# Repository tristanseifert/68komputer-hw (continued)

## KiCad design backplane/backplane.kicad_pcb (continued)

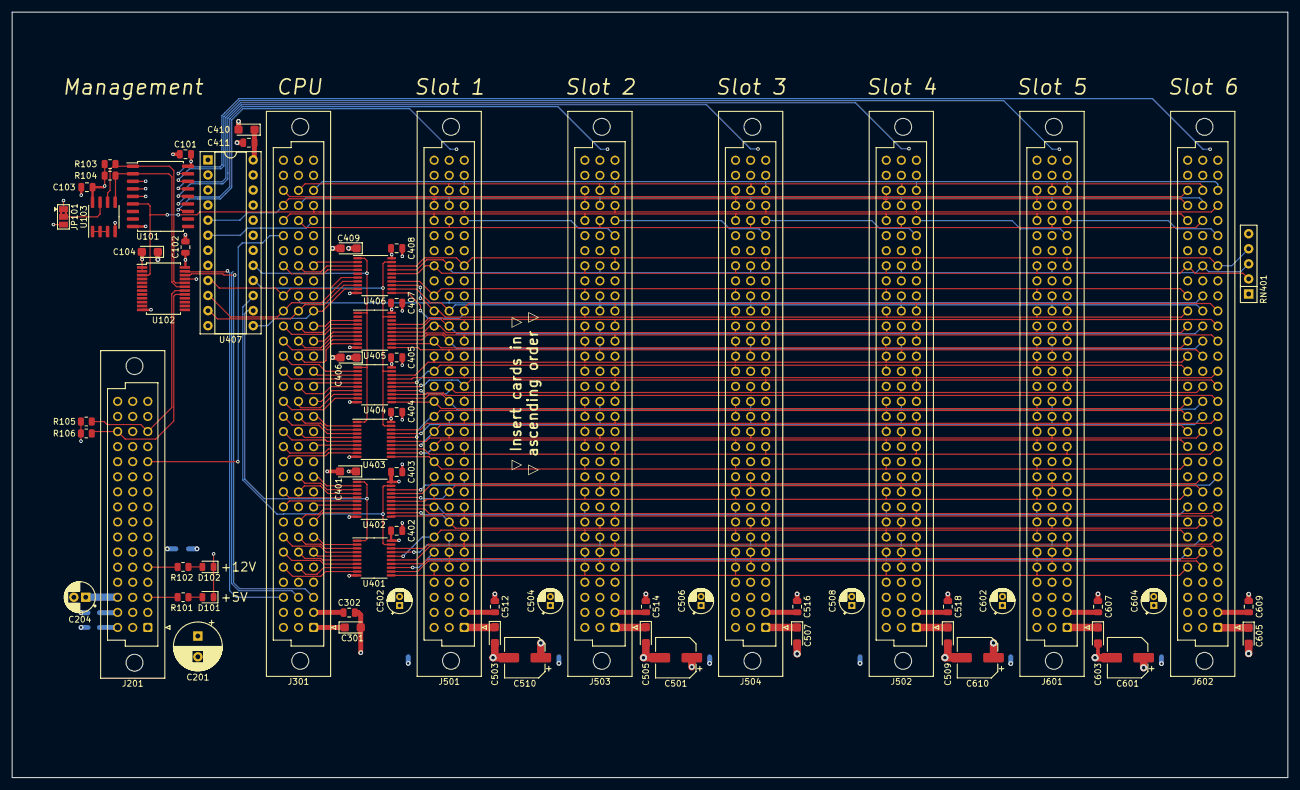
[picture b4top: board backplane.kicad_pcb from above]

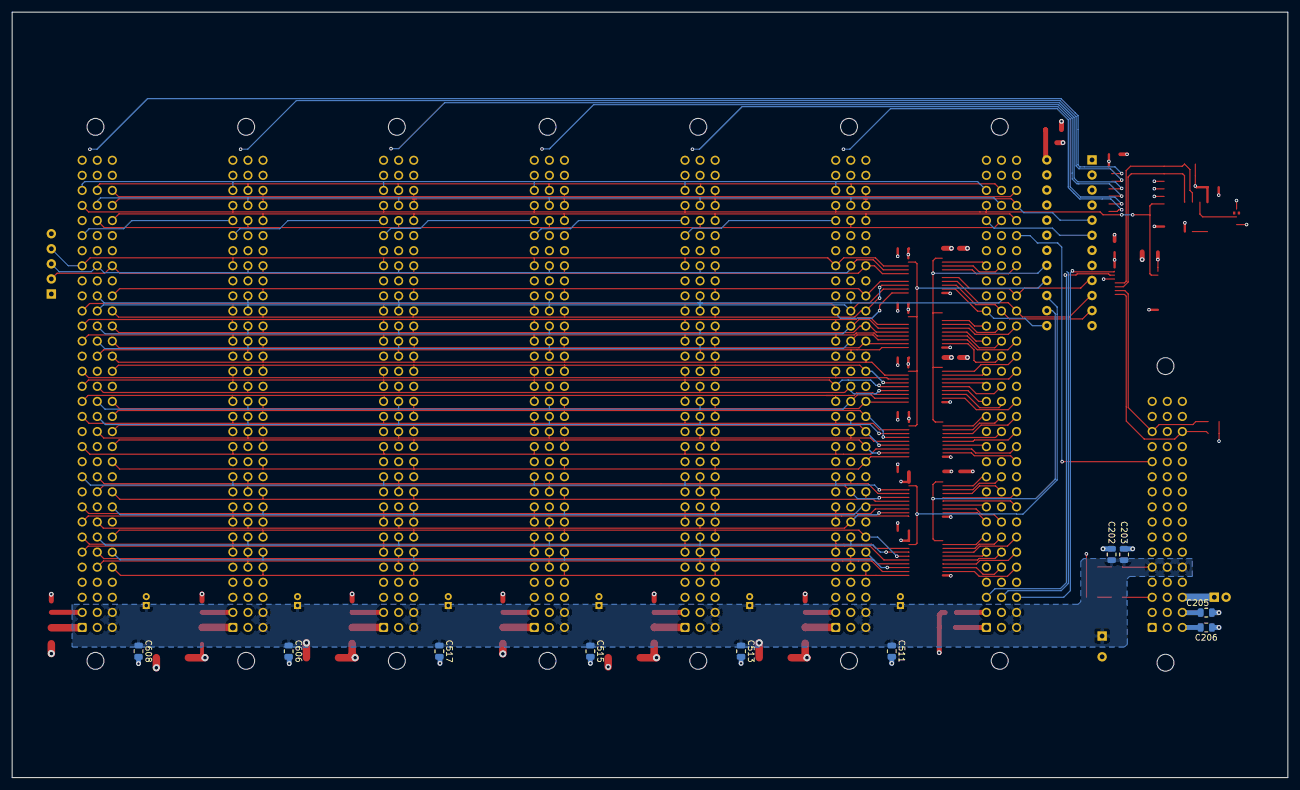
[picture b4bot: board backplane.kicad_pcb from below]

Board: 4 copper layers, 215.0 x 129.0 mm, 79 parts (10 on the bottom side), 132 nets.

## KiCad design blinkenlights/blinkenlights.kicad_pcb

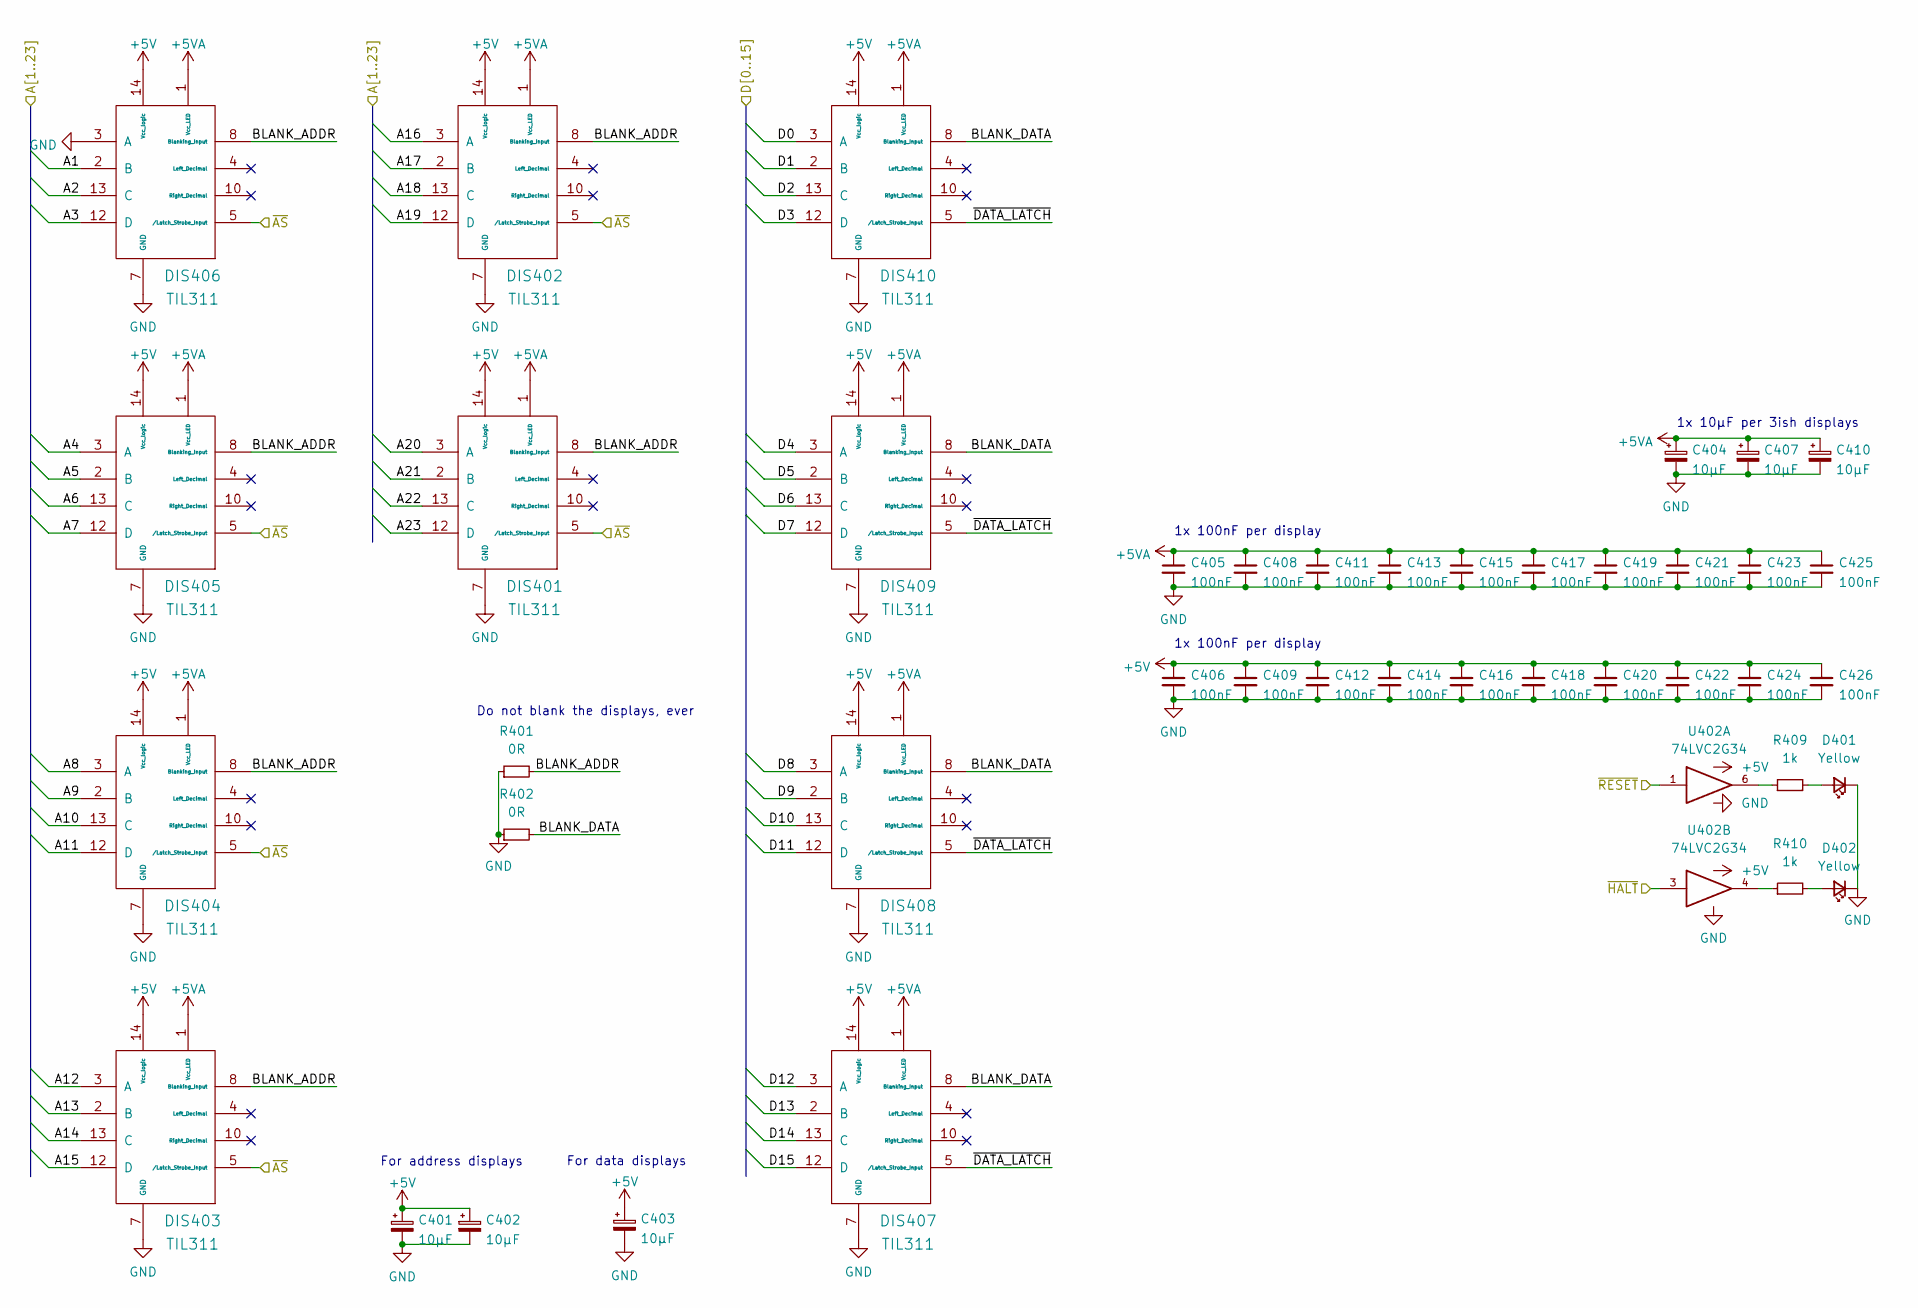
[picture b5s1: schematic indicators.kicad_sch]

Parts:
C401, C402, C403, C404, C407, C410: 10µF; CP_EIA-3216-18_Kemet-A; MPN TAJB106K025SNJ
C405, C406, C408, C409, C411, C412, C413, C414, C415, C416, C417, C418, C419, C420, C421, C422, C423, C424, C425, C426: 100nF; C_0805_2012Metric
D401, D402: Yellow; LED_0805_2012Metric; MPN AP2012YD
DIS401, DIS402, DIS403, DIS404, DIS405, DIS406, DIS407, DIS408, DIS409, DIS410: TIL311
R401, R402: 0R; R_0805_2012Metric; MPN RC0805JR-100RL
R409, R410: 1k; R_0805_2012Metric
U402: 74LVC2G34; SOT-363_SC-70-6_Handsoldering; MPN 74LVC2G34DW-7

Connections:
+5V: C401.1, C402.1, C403.1, C406.1, C409.1, C412.1, C414.1, C416.1, C418.1, C420.1, C422.1, C424.1, C426.1, DIS401.14 (Vcc_logic), DIS402.14 (Vcc_logic), DIS403.14 (Vcc_logic), DIS404.14 (Vcc_logic), DIS405.14 (Vcc_logic), DIS406.14 (Vcc_logic), DIS407.14 (Vcc_logic), DIS408.14 (Vcc_logic), DIS409.14 (Vcc_logic), DIS410.14 (Vcc_logic), U402.5 (VCC); also elsewhere on the board
+5VA: C404.1, C405.1, C407.1, C408.1, C410.1, C411.1, C413.1, C415.1, C417.1, C419.1, C421.1, C423.1, C425.1, DIS401.1 (Vcc_LED), DIS402.1 (Vcc_LED), DIS403.1 (Vcc_LED), DIS404.1 (Vcc_LED), DIS405.1 (Vcc_LED), DIS406.1 (Vcc_LED), DIS407.1 (Vcc_LED), DIS408.1 (Vcc_LED), DIS409.1 (Vcc_LED), DIS410.1 (Vcc_LED); also elsewhere on the board
/A1: DIS406.2 (B); also elsewhere on the board
/A2: DIS406.13 (C); also elsewhere on the board
/A3: DIS406.12 (D); also elsewhere on the board
/A4: DIS405.3 (A); also elsewhere on the board
/A5: DIS405.2 (B); also elsewhere on the board
/A6: DIS405.13 (C); also elsewhere on the board
/A7: DIS405.12 (D); also elsewhere on the board
/A8: DIS404.3 (A); also elsewhere on the board
/A9: DIS404.2 (B); also elsewhere on the board
/A10: DIS404.13 (C); also elsewhere on the board
/A11: DIS404.12 (D); also elsewhere on the board
/A12: DIS403.3 (A); also elsewhere on the board
/A13: DIS403.2 (B); also elsewhere on the board
/A14: DIS403.13 (C); also elsewhere on the board
/A15: DIS403.12 (D); also elsewhere on the board
/A16: DIS402.3 (A); also elsewhere on the board
/A17: DIS402.2 (B); also elsewhere on the board
/A18: DIS402.13 (C); also elsewhere on the board
/A19: DIS402.12 (D); also elsewhere on the board
/A20: DIS401.3 (A); also elsewhere on the board
/A21: DIS401.2 (B); also elsewhere on the board
/A22: DIS401.13 (C); also elsewhere on the board
/A23: DIS401.12 (D); also elsewhere on the board
/D0: DIS410.3 (A); also elsewhere on the board
/D1: DIS410.2 (B); also elsewhere on the board
/D2: DIS410.13 (C); also elsewhere on the board
/D3: DIS410.12 (D); also elsewhere on the board
/D4: DIS409.3 (A); also elsewhere on the board
/D5: DIS409.2 (B); also elsewhere on the board
/D6: DIS409.13 (C); also elsewhere on the board
/D7: DIS409.12 (D); also elsewhere on the board
/D8: DIS408.3 (A); also elsewhere on the board
/D9: DIS408.2 (B); also elsewhere on the board
/D10: DIS408.13 (C); also elsewhere on the board
/D11: DIS408.12 (D); also elsewhere on the board
/D12: DIS407.3 (A); also elsewhere on the board
/D13: DIS407.2 (B); also elsewhere on the board
/D14: DIS407.13 (C); also elsewhere on the board
/D15: DIS407.12 (D); also elsewhere on the board
/Displays and Indicators/BLANK_ADDR: DIS401.8 (Blanking_Input), DIS402.8 (Blanking_Input), DIS403.8 (Blanking_Input), DIS404.8 (Blanking_Input), DIS405.8 (Blanking_Input), DIS406.8 (Blanking_Input), R401.2
/Displays and Indicators/BLANK_DATA: DIS407.8 (Blanking_Input), DIS408.8 (Blanking_Input), DIS409.8 (Blanking_Input), DIS410.8 (Blanking_Input), R402.2
/Displays and Indicators/~DATA_LATCH: DIS407.5 (/Latch_Strobe_Input), DIS408.5 (/Latch_Strobe_Input), DIS409.5 (/Latch_Strobe_Input), DIS410.5 (/Latch_Strobe_Input)
/~AS: DIS401.5 (/Latch_Strobe_Input), DIS402.5 (/Latch_Strobe_Input), DIS403.5 (/Latch_Strobe_Input), DIS404.5 (/Latch_Strobe_Input), DIS405.5 (/Latch_Strobe_Input), DIS406.5 (/Latch_Strobe_Input); also elsewhere on the board
/~HALT: U402.3; also elsewhere on the board
/~RESET: U402.1; also elsewhere on the board
GND: C401.2, C402.2, C403.2, C404.2, C405.2, C406.2, C407.2, C408.2, C409.2, C410.2, C411.2, C412.2, C413.2, C414.2, C415.2, C416.2, C417.2, C418.2, C419.2, C420.2, C421.2, C422.2, C423.2, C424.2, C425.2, C426.2, D401.1 (K), D402.1 (K), DIS401.7 (GND), DIS402.7 (GND), DIS403.7 (GND), DIS404.7 (GND), DIS405.7 (GND), DIS406.3 (A), DIS406.7 (GND), DIS407.7 (GND), DIS408.7 (GND), DIS409.7 (GND), DIS410.7 (GND), R401.1, R402.1, U402.2 (GND); also elsewhere on the board
unnamed: D401.2 (A), R409.2
unnamed: D402.2 (A), R410.2
unnamed: R409.1, U402.6
unnamed: R410.1, U402.4

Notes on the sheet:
1x 10µF per 3ish displays
1x 100nF per display
For address displays
For data displays
Do not blank the displays, ever

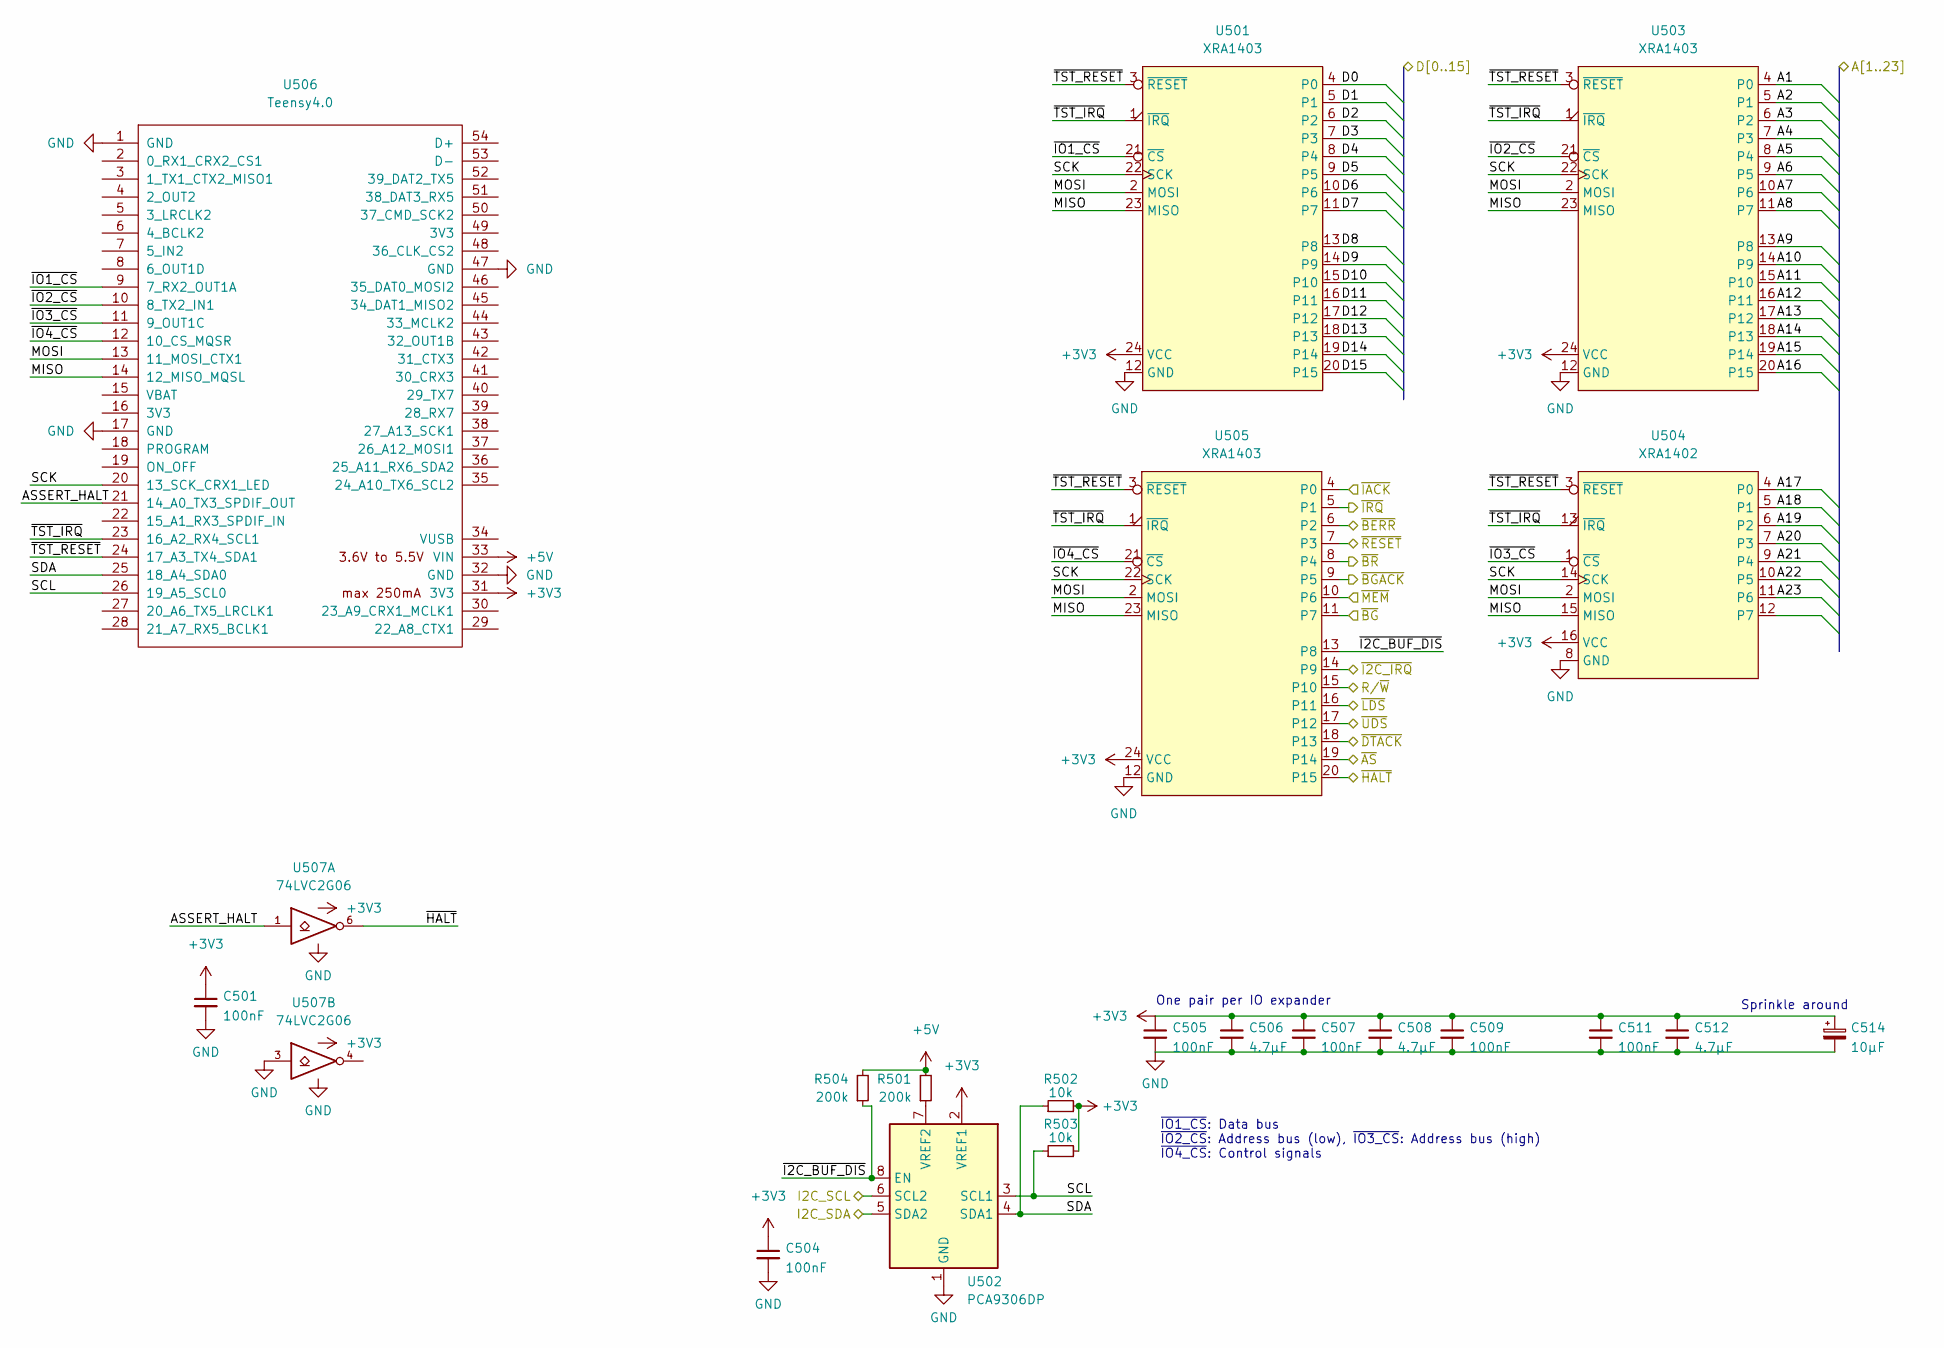
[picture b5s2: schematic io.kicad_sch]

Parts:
C501, C504, C505, C507, C509, C511: 100nF; C_0805_2012Metric
C506, C508, C512: 4.7µF; C_0805_2012Metric
C514: 10µF; CP_EIA-3216-18_Kemet-A; MPN TAJB106K025SNJ
R501, R504: 200k; R_0805_2012Metric
R502, R503: 10k; R_0805_2012Metric
U501, U503, U505: XRA1403; TSSOP-24_4.4x7.8mm_P0.65mm
U502: PCA9306DP; SO-8_3.9x4.9mm_P1.27mm
U504: XRA1402; TSSOP-16_4.4x5mm_P0.65mm
U506: Teensy4.0; Teensy40-NoBonus
U507: 74LVC2G06; SOT-23-6_Handsoldering

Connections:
+3V3: C501.1, C504.1, C505.1, C506.1, C507.1, C508.1, C509.1, C511.1, C512.1, C514.1, R502.2, R503.2, U501.24 (VCC), U502.2 (VREF1), U503.24 (VCC), U504.16 (VCC), U505.24 (VCC), U506.31 (3V3), U507.5 (VCC); also elsewhere on the board
+5V: R501.2, R504.2, U506.33 (VIN); also elsewhere on the board
/A1: U503.4 (P0); also elsewhere on the board
/A2: U503.5 (P1); also elsewhere on the board
/A3: U503.6 (P2); also elsewhere on the board
/A4: U503.7 (P3); also elsewhere on the board
/A5: U503.8 (P4); also elsewhere on the board
/A6: U503.9 (P5); also elsewhere on the board
/A7: U503.10 (P6); also elsewhere on the board
/A8: U503.11 (P7); also elsewhere on the board
/A9: U503.13 (P8); also elsewhere on the board
/A10: U503.14 (P9); also elsewhere on the board
/A11: U503.15 (P10); also elsewhere on the board
/A12: U503.16 (P11); also elsewhere on the board
/A13: U503.17 (P12); also elsewhere on the board
/A14: U503.18 (P13); also elsewhere on the board
/A15: U503.19 (P14); also elsewhere on the board
/A16: U503.20 (P15); also elsewhere on the board
/A17: U504.4 (P0); also elsewhere on the board
/A18: U504.5 (P1); also elsewhere on the board
/A19: U504.6 (P2); also elsewhere on the board
/A20: U504.7 (P3); also elsewhere on the board
/A21: U504.9 (P4); also elsewhere on the board
/A22: U504.10 (P5); also elsewhere on the board
/A23: U504.11 (P6); also elsewhere on the board
/D0: U501.4 (P0); also elsewhere on the board
/D1: U501.5 (P1); also elsewhere on the board
/D2: U501.6 (P2); also elsewhere on the board
/D3: U501.7 (P3); also elsewhere on the board
/D4: U501.8 (P4); also elsewhere on the board
/D5: U501.9 (P5); also elsewhere on the board
/D6: U501.10 (P6); also elsewhere on the board
/D7: U501.11 (P7); also elsewhere on the board
/D8: U501.13 (P8); also elsewhere on the board
/D9: U501.14 (P9); also elsewhere on the board
/D10: U501.15 (P10); also elsewhere on the board
/D11: U501.16 (P11); also elsewhere on the board
/D12: U501.17 (P12); also elsewhere on the board
/D13: U501.18 (P13); also elsewhere on the board
/D14: U501.19 (P14); also elsewhere on the board
/D15: U501.20 (P15); also elsewhere on the board
/I2C_SCL: U502.6 (SCL2); also elsewhere on the board
/I2C_SDA: U502.5 (SDA2); also elsewhere on the board
/IO Drivers/ASSERT_HALT: U506.21 (14_A0_TX3_SPDIF_OUT), U507.1
/IO Drivers/CTRL_DIR: U506.29 (22_A8_CTX1); also elsewhere on the board
/IO Drivers/MISO: U501.23 (MISO), U503.23 (MISO), U504.15 (MISO), U505.23 (MISO), U506.14 (12_MISO_MQSL)
/IO Drivers/MOSI: U501.2 (MOSI), U503.2 (MOSI), U504.2 (MOSI), U505.2 (MOSI), U506.13 (11_MOSI_CTX1)
/IO Drivers/R/~W_3V3: U506.27 (20_A6_TX5_LRCLK1); also elsewhere on the board
/IO Drivers/SCK: U501.22 (SCK), U503.22 (SCK), U504.14 (SCK), U505.22 (SCK), U506.20 (13_SCK_CRX1_LED)
/IO Drivers/SCL: R503.1, U502.3 (SCL1), U506.26 (19_A5_SCL0)
/IO Drivers/SDA: R502.1, U502.4 (SDA1), U506.25 (18_A4_SDA0)
/IO Drivers/~AS_3V3: U506.28 (21_A7_RX5_BCLK1); also elsewhere on the board
/IO Drivers/~BERR_3V3: U506.7 (5_IN2); also elsewhere on the board
/IO Drivers/~DTACK_3V3: U506.8 (6_OUT1D); also elsewhere on the board
/IO Drivers/~I2C_BUF_DIS: R504.1, U502.8 (EN), U505.13 (P8)
/IO Drivers/~IO1_CS: U501.21 (~CS), U506.9 (7_RX2_OUT1A)
/IO Drivers/~IO2_CS: U503.21 (~CS), U506.10 (8_TX2_IN1)
/IO Drivers/~IO3_CS: U504.1 (~CS), U506.11 (9_OUT1C)
/IO Drivers/~IO4_CS: U505.21 (~CS), U506.12 (10_CS_MQSR)
/IO Drivers/~TST_IRQ: U501.1 (~IRQ), U503.1 (~IRQ), U504.13 (~IRQ), U505.1 (~IRQ), U506.23 (16_A2_RX4_SCL1)
/IO Drivers/~TST_RESET: U501.3 (~RESET), U503.3 (~RESET), U504.3 (~RESET), U505.3 (~RESET), U506.24 (17_A3_TX4_SDA1)
/R/~W: U505.15 (P10); also elsewhere on the board
/~AS: U505.19 (P14); also elsewhere on the board
/~BERR: U505.6 (P2); also elsewhere on the board
/~BGACK: U505.9 (P5); also elsewhere on the board
/~BG: U505.11 (P7); also elsewhere on the board
/~BR: U505.8 (P4); also elsewhere on the board
/~DTACK: U505.18 (P13); also elsewhere on the board
/~HALT: U505.20 (P15), U507.6; also elsewhere on the board
/~I2C_IRQ: U505.14 (P9); also elsewhere on the board
/~IACK: U505.4 (P0); also elsewhere on the board
/~IRQ: U505.5 (P1); also elsewhere on the board
/~LDS: U505.16 (P11); also elsewhere on the board
/~MEM: U505.10 (P6); also elsewhere on the board
/~RESET: U505.7 (P3); also elsewhere on the board
/~UDS: U505.17 (P12); also elsewhere on the board
GND: C501.2, C504.2, C505.2, C506.2, C507.2, C508.2, C509.2, C511.2, C512.2, C514.2, U501.12 (GND), U502.1 (GND), U503.12 (GND), U504.8 (GND), U505.12 (GND), U506.1 (GND), U506.17 (GND), U506.32 (GND), U506.47 (GND), U507.2 (GND), U507.3; also elsewhere on the board
unnamed: R501.1, U502.7 (VREF2)

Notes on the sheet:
Sprinkle around
~{IO1_CS}: Data bus ~{IO2_CS}: Address bus (low), ~{IO3_CS}: Address bus (high) ~{IO4_CS}: Control signals
One pair per IO expander

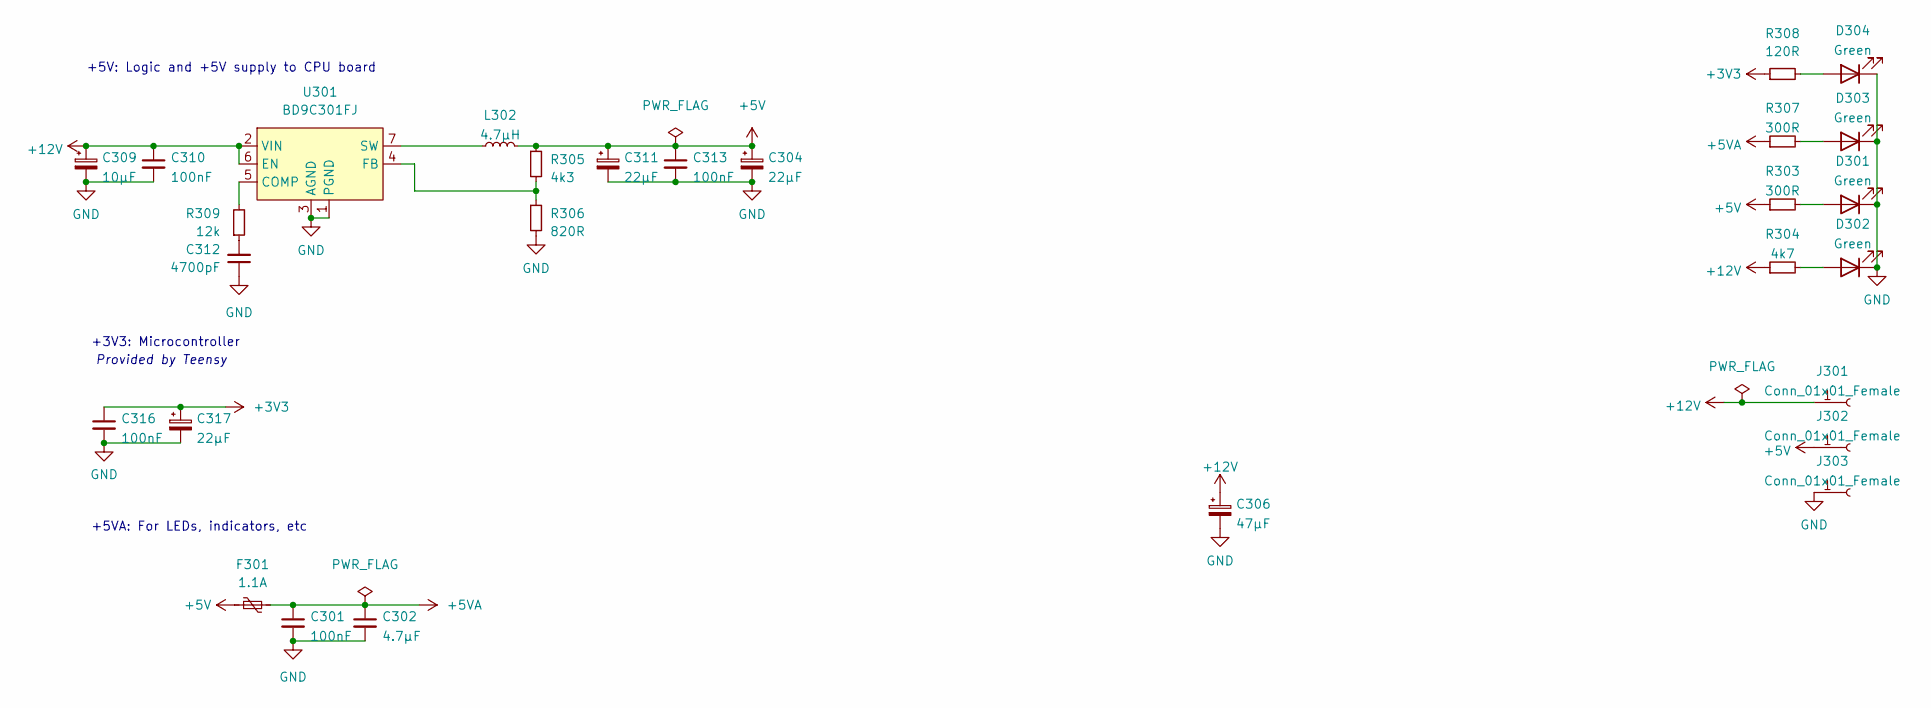
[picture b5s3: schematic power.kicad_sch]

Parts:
C301, C310, C313, C316: 100nF; C_0805_2012Metric
C302: 4.7µF; C_0805_2012Metric
C304, C311, C317: 22µF; CP_EIA-3528-21_Kemet-B; MPN TAJB226K016UNJ
C306: 47µF; CP_Radial_D6.3mm_P2.50mm; MPN A750EK476M1EAAE040
C309: 10µF; CP_EIA-3528-21_Kemet-B; MPN TAJB106K025SNJ
C312: 4700pF; C_0805_2012Metric
D301, D302, D303, D304: Green; LED_0805_2012Metric; MPN 150080GS75000
F301: 1.1A; Fuse_Bourns_MF-SM_7.98x5.44mm; MPN 652-MFSM100-2
J301, J302, J303: Conn_01x01_Female; DELTRON-571-0x00
L302: 4.7µH; L_Taiyo-Yuden_NR-80xx_HandSoldering; MPN NRS8040T4R7NJGJ
R303, R307: 300R; R_0805_2012Metric
R304: 4k7; R_0805_2012Metric
R305: 4k3; R_0805_2012Metric
R306: 820R; R_0805_2012Metric
R308: 120R; R_0805_2012Metric
R309: 12k; R_0805_2012Metric
U301: BD9C301FJ; SOP-8_3.9x4.9mm_P1.27mm

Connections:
+3V3: C316.1, C317.1, R308.1; also elsewhere on the board
+5V: C304.1, C311.1, C313.1, F301.2, J302.1, L302.2, R303.1, R305.1; also elsewhere on the board
+5VA: C301.1, C302.1, F301.1, R307.1; also elsewhere on the board
+12V: C306.1, C309.1, C310.1, J301.1, R304.1, U301.2 (VIN), U301.6 (EN); also elsewhere on the board
GND: C301.2, C302.2, C304.2, C306.2, C309.2, C310.2, C311.2, C312.1, C313.2, C316.2, C317.2, D301.1 (K), D302.1 (K), D303.1 (K), D304.1 (K), J303.1, R306.2, U301.1 (PGND), U301.3 (AGND); also elsewhere on the board
unnamed: C312.2, R309.1
unnamed: D301.2 (A), R303.2
unnamed: D302.2 (A), R304.2
unnamed: D303.2 (A), R307.2
unnamed: D304.2 (A), R308.2
unnamed: L302.1, U301.7 (SW), U301.8 (SW)
unnamed: R305.2, R306.1, U301.4 (FB)
unnamed: R309.2, U301.5 (COMP)

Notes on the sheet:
+5V: Logic and +5V supply to CPU board
+3V3: Microcontroller
Provided by Teensy
+5VA: For LEDs, indicators, etc

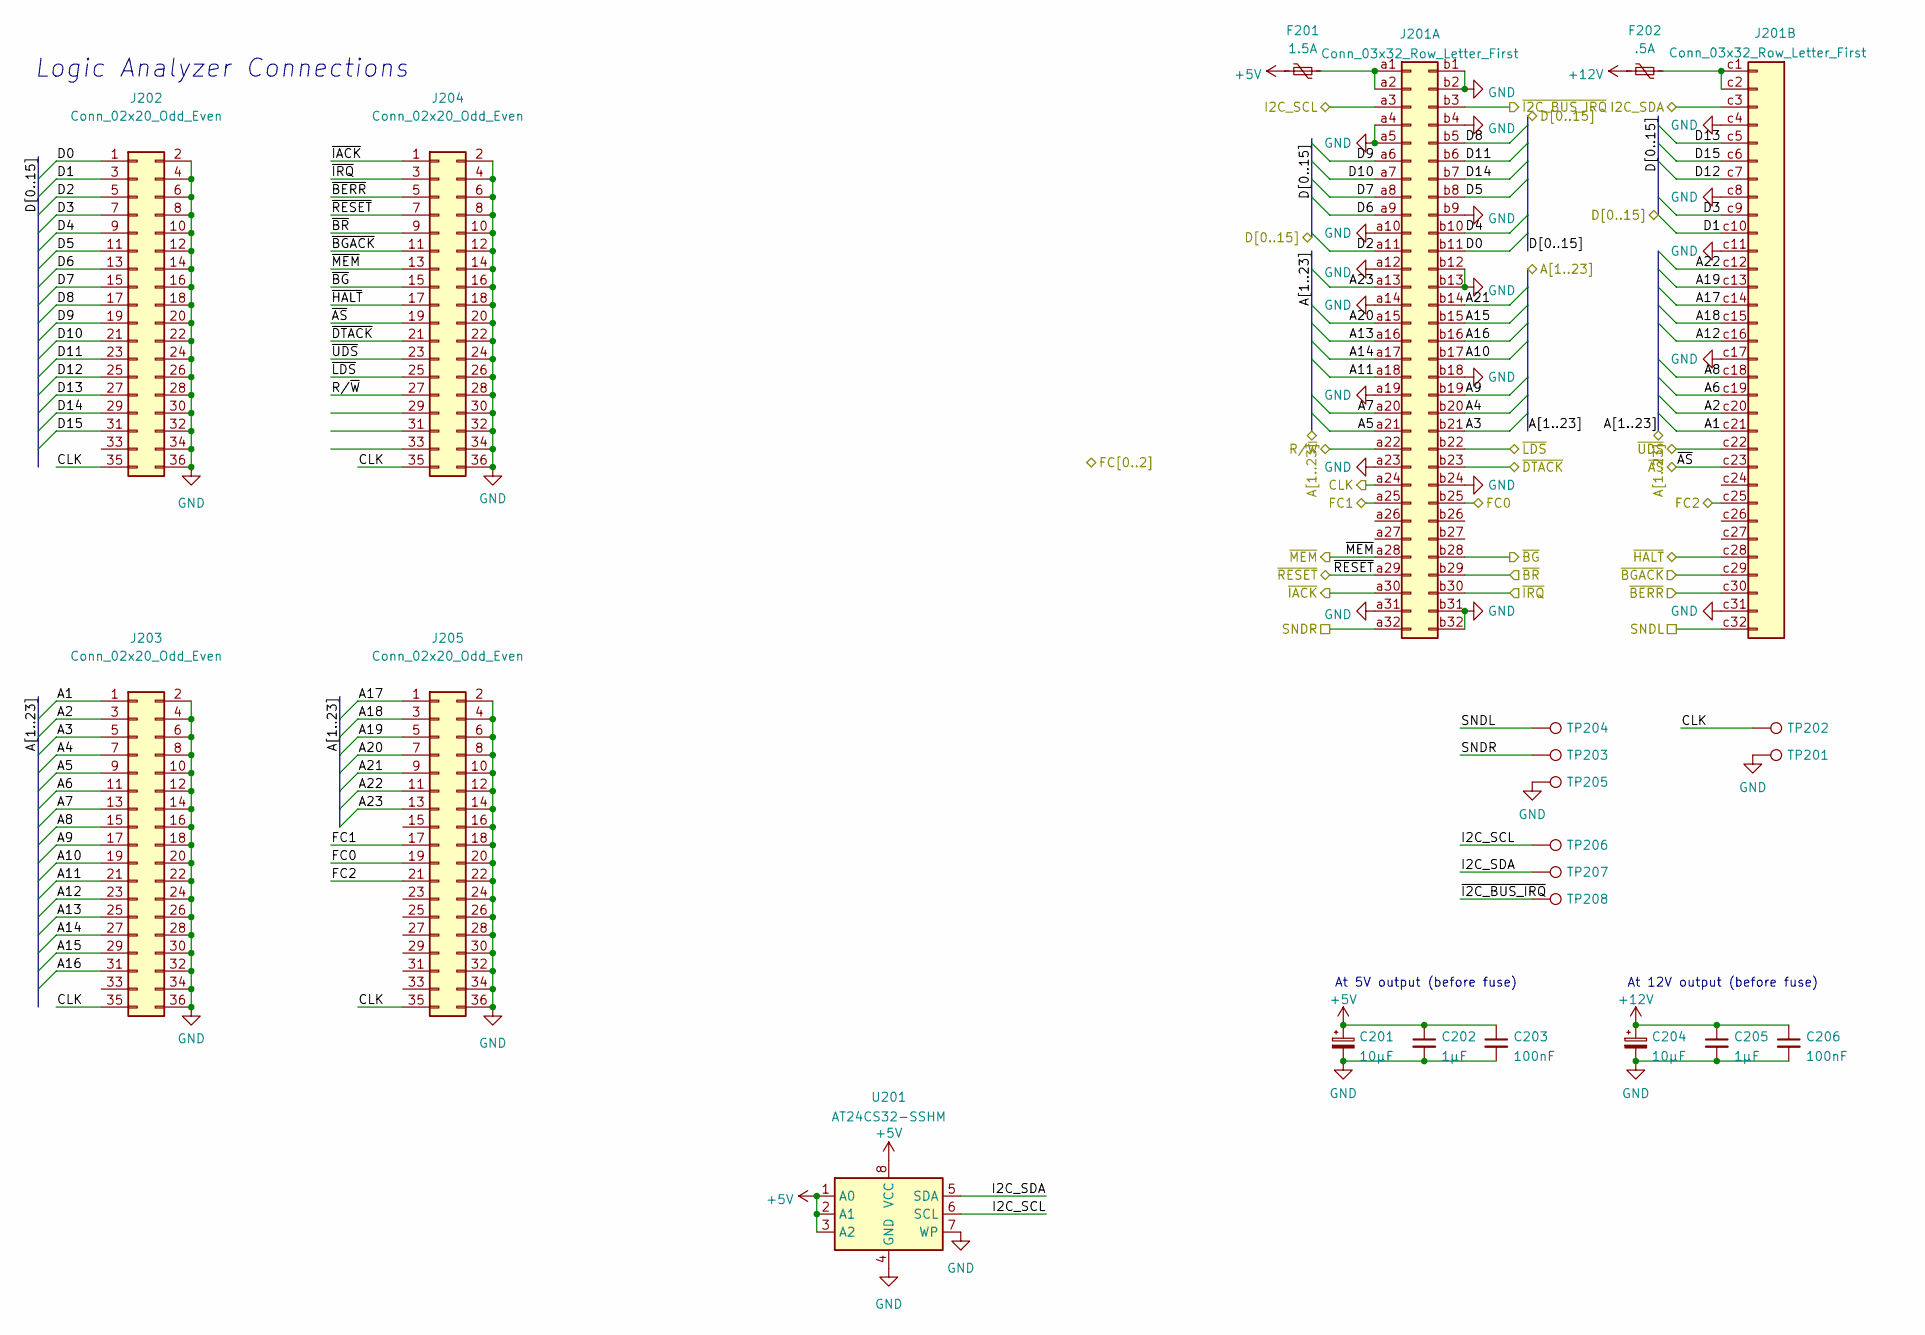
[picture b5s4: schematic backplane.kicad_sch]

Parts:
C201: 10µF; CP_EIA-3216-18_Kemet-A; MPN TAJB106K025SNJ
C202, C205: 1µF; C_0805_2012Metric
C203, C206: 100nF; C_0805_2012Metric
C204: 10µF; CP_EIA-3528-21_Kemet-B; MPN TAJB106K025SNJ
F201: 1.5A; Fuse_Bourns_MF-SM_7.98x5.44mm; MPN MF-SM150/33-2
F202: .5A; Fuse_Littelfuse-NANO2-451_453; MPN NANOSMDC050F/13.2-2
J201: Conn_03x32_Row_Letter_First; DIN41612_C_3x32_Female_Vertical_THT
J202, J203, J204, J205: Conn_02x20_Odd_Even; PinHeader_2x18_P2.54mm_Vertical
TP201, TP202, TP203, TP204, TP205, TP206, TP207, TP208: TestPoint; TestPoint_Loop_D2.60mm_Drill1.4mm_Beaded; MPN 534-5001
U201: AT24CS32-SSHM; SOIC-8_3.9x4.9mm_P1.27mm; MPN AT24CS32-SSHM-T

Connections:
+5V: C201.1, C202.1, C203.1, F201.2, U201.1 (A0), U201.2 (A1), U201.3 (A2), U201.8 (VCC); also elsewhere on the board
+12V: C204.1, C205.1, C206.1, F202.2; also elsewhere on the board
/A1: J201.c21, J203.1; also elsewhere on the board
/A2: J201.c20, J203.3; also elsewhere on the board
/A3: J201.b21, J203.5; also elsewhere on the board
/A4: J201.b20, J203.7; also elsewhere on the board
/A5: J201.a21, J203.9; also elsewhere on the board
/A6: J201.c19, J203.11; also elsewhere on the board
/A7: J201.a20, J203.13; also elsewhere on the board
/A8: J201.c18, J203.15; also elsewhere on the board
/A9: J201.b19, J203.17; also elsewhere on the board
/A10: J201.b17, J203.19; also elsewhere on the board
/A11: J201.a18, J203.21; also elsewhere on the board
/A12: J201.c16, J203.23; also elsewhere on the board
/A13: J201.a16, J203.25; also elsewhere on the board
/A14: J201.a17, J203.27; also elsewhere on the board
/A15: J201.b15, J203.29; also elsewhere on the board
/A16: J201.b16, J203.31; also elsewhere on the board
/A17: J201.c14, J205.1; also elsewhere on the board
/A18: J201.c15, J205.3; also elsewhere on the board
/A19: J201.c13, J205.5; also elsewhere on the board
/A20: J201.a15, J205.7; also elsewhere on the board
/A21: J201.b14, J205.9; also elsewhere on the board
/A22: J201.c12, J205.11; also elsewhere on the board
/A23: J201.a13, J205.13; also elsewhere on the board
/CLK: J201.a24, J202.35, J203.35, J204.35, J205.35, TP202.1
/D0: J201.b11, J202.1; also elsewhere on the board
/D1: J201.c10, J202.3; also elsewhere on the board
/D2: J201.a11, J202.5; also elsewhere on the board
/D3: J201.c9, J202.7; also elsewhere on the board
/D4: J201.b10, J202.9; also elsewhere on the board
/D5: J201.b8, J202.11; also elsewhere on the board
/D6: J201.a9, J202.13; also elsewhere on the board
/D7: J201.a8, J202.15; also elsewhere on the board
/D8: J201.b5, J202.17; also elsewhere on the board
/D9: J201.a6, J202.19; also elsewhere on the board
/D10: J201.a7, J202.21; also elsewhere on the board
/D11: J201.b6, J202.23; also elsewhere on the board
/D12: J201.c7, J202.25; also elsewhere on the board
/D13: J201.c5, J202.27; also elsewhere on the board
/D14: J201.b7, J202.29; also elsewhere on the board
/D15: J201.c6, J202.31; also elsewhere on the board
/FC0: J201.b25, J205.19
/FC1: J201.a25, J205.17
/FC2: J201.c25, J205.21
/I2C_SCL: J201.a3, TP206.1, U201.6 (SCL); also elsewhere on the board
/I2C_SDA: J201.c3, TP207.1, U201.5 (SDA); also elsewhere on the board
/R/~W: J201.a22, J204.27; also elsewhere on the board
/SNDL: J201.c32, TP204.1
/SNDR: J201.a32, TP203.1
/~AS: J201.c23, J204.19; also elsewhere on the board
/~BERR: J201.c30, J204.5; also elsewhere on the board
/~BGACK: J201.c29, J204.11; also elsewhere on the board
/~BG: J201.b28, J204.15; also elsewhere on the board
/~BR: J201.b29, J204.9; also elsewhere on the board
/~DTACK: J201.b23, J204.21; also elsewhere on the board
/~HALT: J201.c28, J204.17; also elsewhere on the board
/~I2C_IRQ: J201.b3, TP208.1; also elsewhere on the board
/~IACK: J201.a30, J204.1; also elsewhere on the board
/~IRQ: J201.b30, J204.3; also elsewhere on the board
/~LDS: J201.b22, J204.25; also elsewhere on the board
/~MEM: J201.a28, J204.13; also elsewhere on the board
/~RESET: J201.a29, J204.7; also elsewhere on the board
/~UDS: J201.c22, J204.23; also elsewhere on the board
GND: C201.2, C202.2, C203.2, C204.2, C205.2, C206.2, J201.a4, J201.a5, J201.a10, J201.a12, J201.a14, J201.a19, J201.a23, J201.a31, J201.b1, J201.b2, J201.b4, J201.b9, J201.b12, J201.b13, J201.b18, J201.b24, J201.b31, J201.b32, J201.c4, J201.c8, J201.c11, J201.c17, J201.c31, J202.2, J202.4, J202.6, J202.8, J202.10, J202.12, J202.14, J202.16, J202.18, J202.20, J202.22, J202.24, J202.26, J202.28, J202.30, J202.32, J202.34, J202.36, J203.2, J203.4, J203.6, J203.8, J203.10, J203.12, J203.14, J203.16, J203.18, J203.20, J203.22, J203.24, J203.26, J203.28, J203.30, J203.32, J203.34, J203.36, J204.2, J204.4, J204.6, J204.8, J204.10, J204.12, J204.14, J204.16, J204.18, J204.20, J204.22, J204.24, J204.26, J204.28, J204.30, J204.32, J204.34, J204.36, J205.2, J205.4, J205.6, J205.8, J205.10, J205.12, J205.14, J205.16, J205.18, J205.20, J205.22, J205.24, J205.26, J205.28, J205.30, J205.32, J205.34, J205.36, TP201.1, TP205.1, U201.4 (GND), U201.7 (WP); also elsewhere on the board
unnamed: F201.1, J201.a1, J201.a2
unnamed: F202.1, J201.c1, J201.c2

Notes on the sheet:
At 5V output (before fuse)
At 12V output (before fuse)
Logic Analyzer Connections

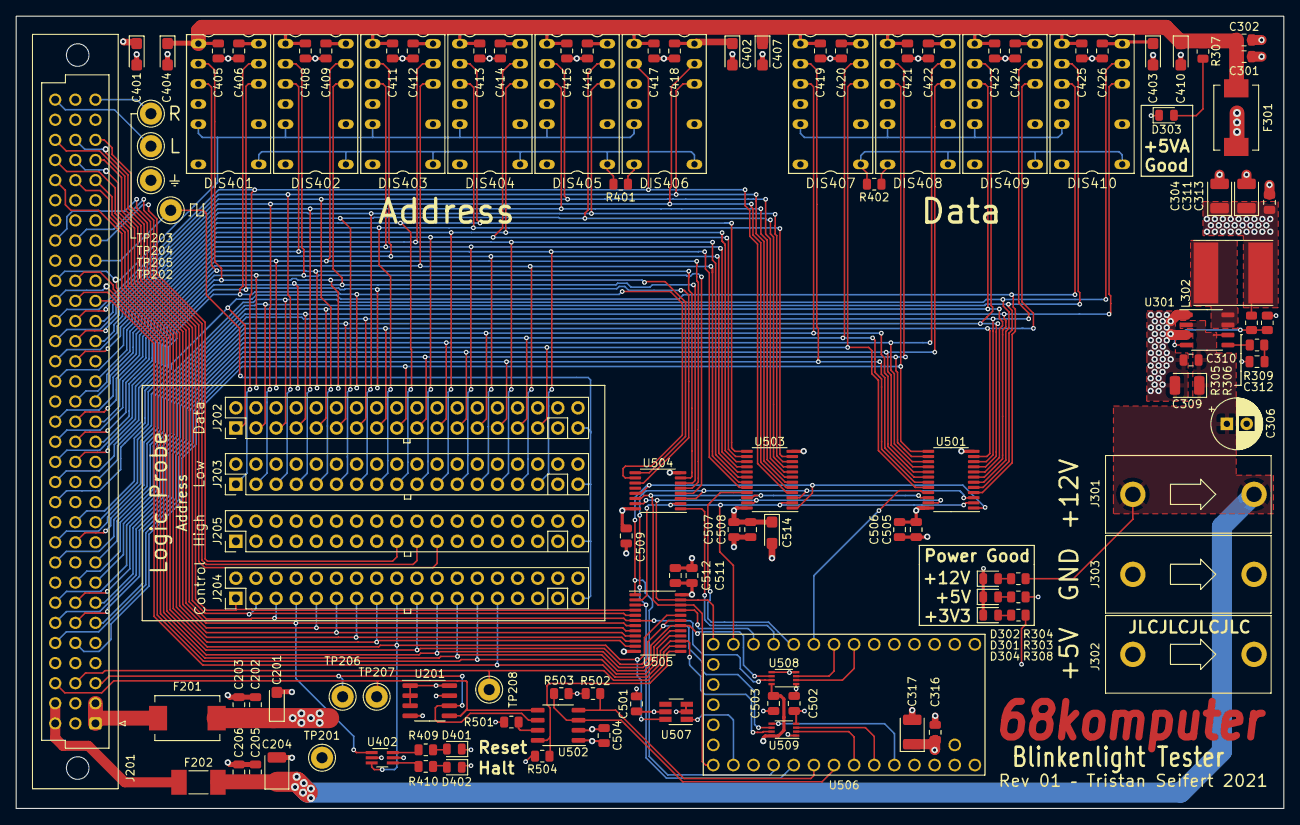
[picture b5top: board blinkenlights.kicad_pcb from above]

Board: 4 copper layers, 160.0 x 100.0 mm, 118 parts (0 on the bottom side), 103 nets.

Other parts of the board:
C502, C503: 100nF; C_0805_2012Metric
U508, U509: 74LVC2T45DC; VSSOP-8_2.3x2mm_P0.5mm

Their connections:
+3V3: C502.1, U508.1 (VCCA), U509.1 (VCCA); also elsewhere on the board
+5V: C503.1, U508.8 (VCCB), U509.8 (VCCB); also elsewhere on the board
/IO Drivers/CTRL_DIR: U509.5 (DIR); also elsewhere on the board
/IO Drivers/R/~W_3V3: U509.2 (1A); also elsewhere on the board
/IO Drivers/~AS_3V3: U509.3 (2A); also elsewhere on the board
/IO Drivers/~BERR_3V3: U508.2 (1A); also elsewhere on the board
/IO Drivers/~DTACK_3V3: U508.3 (2A); also elsewhere on the board
/R/~W: U509.7 (1B); also elsewhere on the board
/~AS: U509.6 (2B); also elsewhere on the board
/~BERR: U508.7 (1B); also elsewhere on the board
/~DTACK: U508.6 (2B); also elsewhere on the board
GND: C502.2, C503.2, U508.4 (GND), U508.5 (DIR), U509.4 (GND); also elsewhere on the board
